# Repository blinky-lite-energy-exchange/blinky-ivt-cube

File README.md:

# Blinky IVT Cube
The Blinky-IVT cube controls an infrared diode to send pulses to an IVT heat pump. The pulse sequence is defined in the IVT.h file in the cubeCode folder. The pulse sequence was modified from [ToniA/arduino-heatpumpir](https://github.com/ToniA/arduino-heatpumpir). The [ToniA/arduino-heatpumpir](https://github.com/ToniA/arduino-heatpumpir) project contains pulse sequences for 29 different models of heat pumps so it possible to easily extend the Blinky IVT cube to many different models of heat pumps. The The microcontroller is a [Raspberry Pi Pico W](https://www.raspberrypi.com/products/raspberry-pi-pico/) that connects wirelessly to soft Blinky-Lite tray the resides on a Blinky-Lite box.

The Blinky IVT Cube sends and receives data from the [Blinky IVT tray](https://github.com/blinky-lite-energy-exchange/blinky-ivt-tray).

<br>

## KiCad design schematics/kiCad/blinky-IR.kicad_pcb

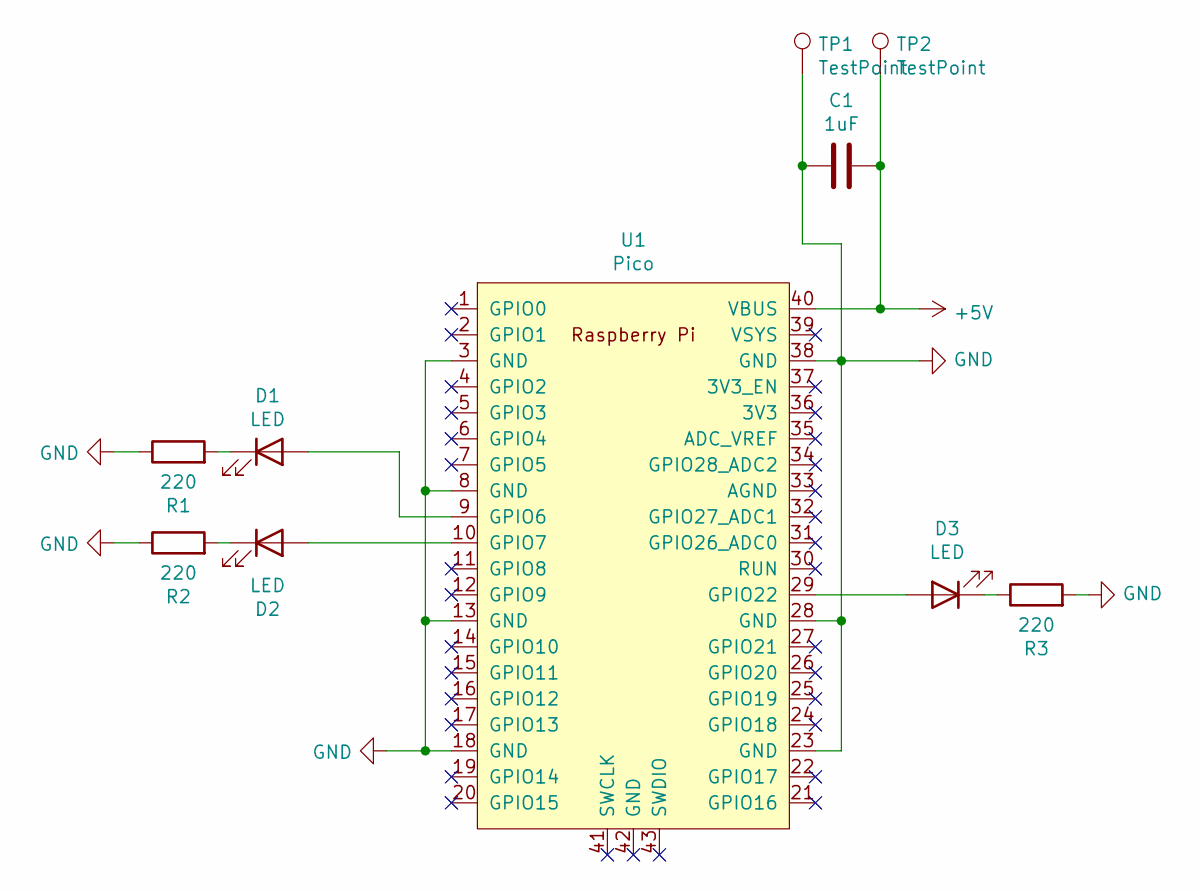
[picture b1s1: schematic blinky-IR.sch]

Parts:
C1: 1uF; C_1206_3216Metric_Pad1.42x1.75mm_HandSolder
D1, D2, D3: LED; LED_D5.0mm
R1, R2, R3: 220; R_1206_3216Metric_Pad1.42x1.75mm_HandSolder
TP1, TP2: TestPoint; TestPoint_THTPad_D2.0mm_Drill1.0mm
U1: Pico; RPi_Pico_SMD_TH

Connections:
+5V: C1.1, TP2.1, U1.40 (VBUS)
GND: C1.2, R1.1, R2.1, R3.2, TP1.1, U1.3 (GND), U1.8 (GND), U1.13 (GND), U1.18 (GND), U1.23 (GND), U1.28 (GND), U1.38 (GND)
unnamed: D1.1 (K), R1.2
unnamed: D1.2 (A), U1.9 (GPIO6)
unnamed: D2.1 (K), R2.2
unnamed: D2.2 (A), U1.10 (GPIO7)
unnamed: D3.1 (K), R3.1
unnamed: D3.2 (A), U1.29 (GPIO22)

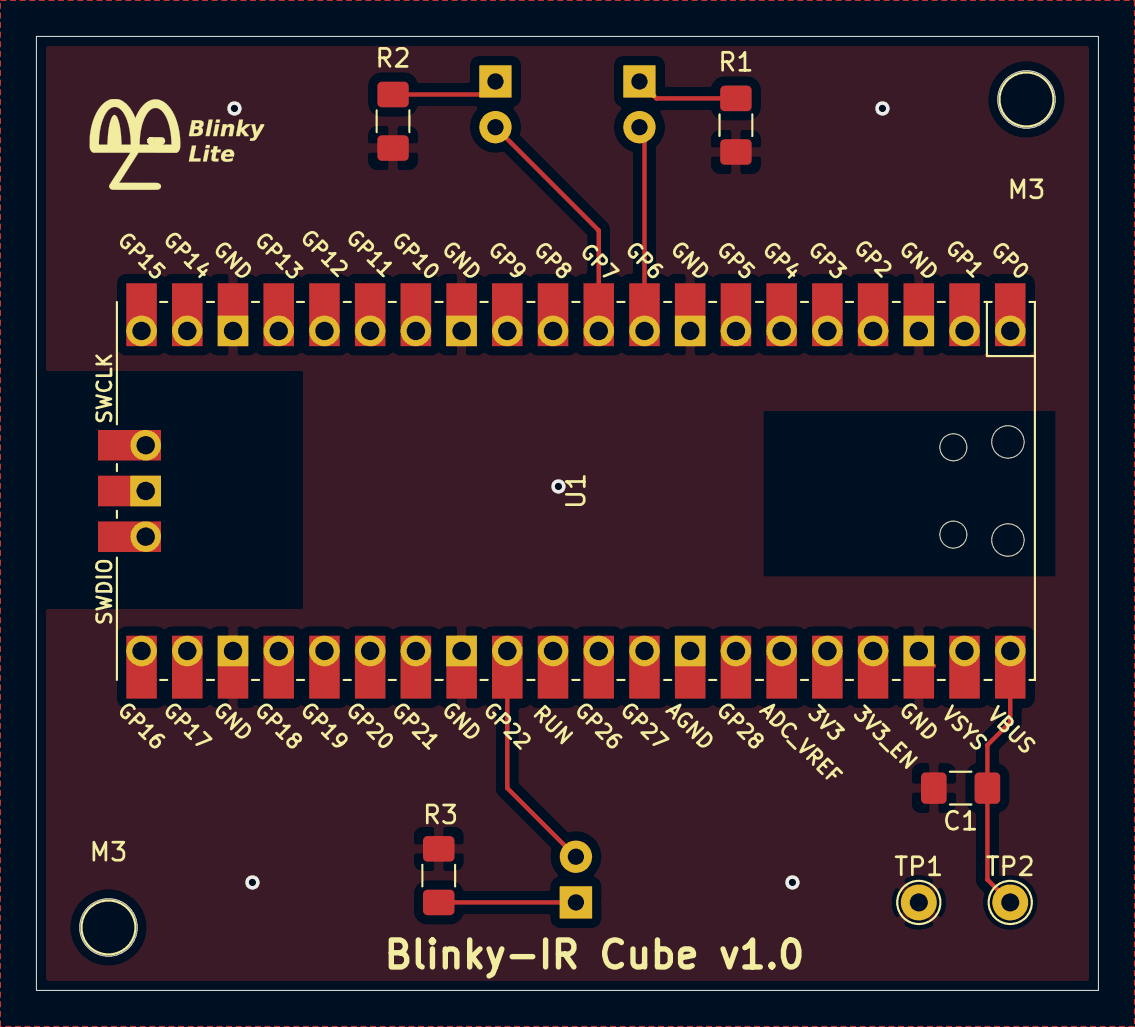
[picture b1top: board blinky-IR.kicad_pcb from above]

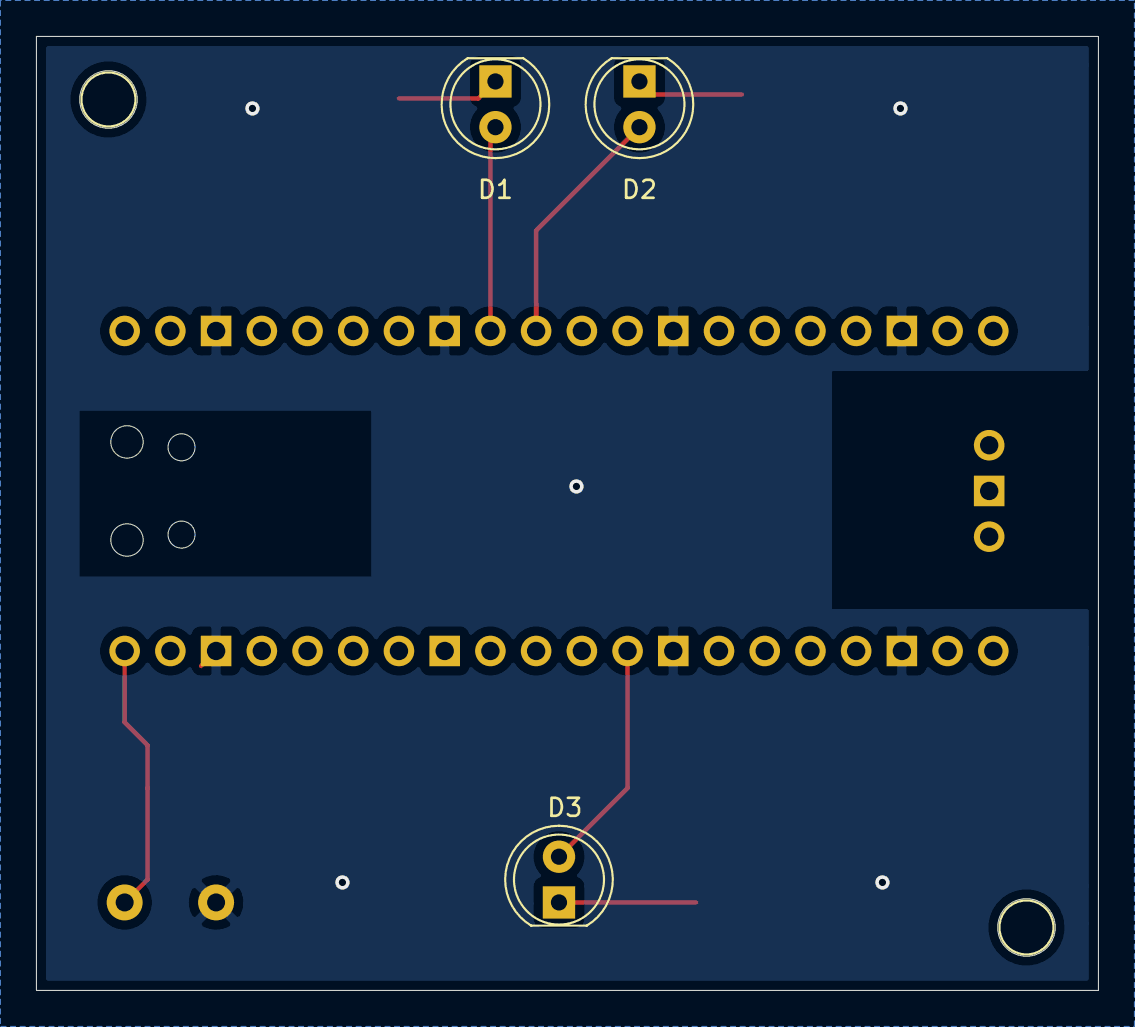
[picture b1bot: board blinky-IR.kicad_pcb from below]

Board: 2 copper layers, 59.0 x 53.0 mm, 12 parts (3 on the bottom side), 8 nets.

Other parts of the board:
M3, M3#2: MountingHole_3.2mm_M3

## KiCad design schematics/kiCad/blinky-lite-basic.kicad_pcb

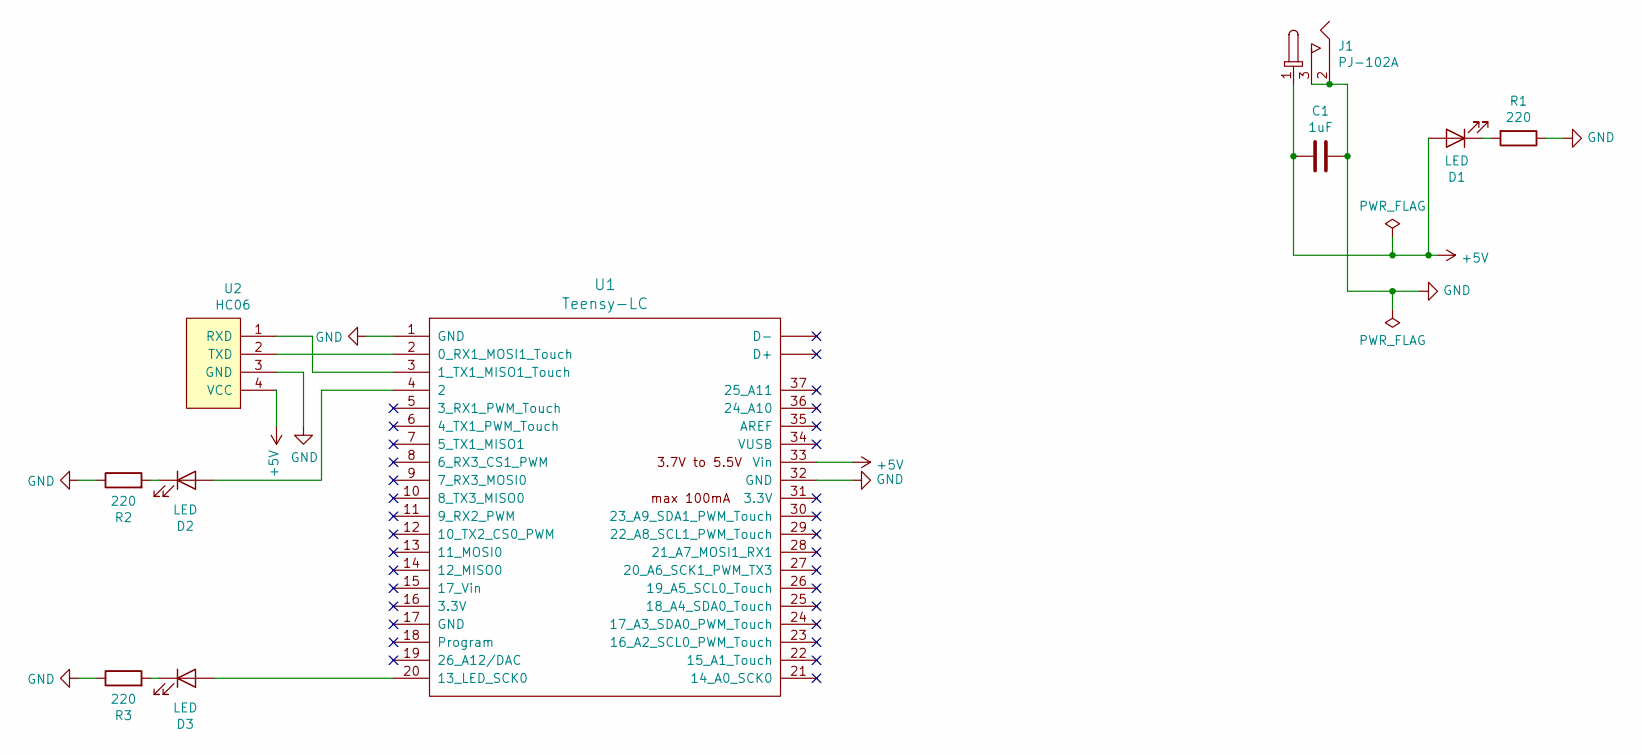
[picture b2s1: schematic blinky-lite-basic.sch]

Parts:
C1: 1uF; C_1206_3216Metric_Pad1.42x1.75mm_HandSolder
D1, D2, D3: LED; LED_D5.0mm
J1: PJ-102A; DC21Jack
R1, R2, R3: 220; R_1206_3216Metric_Pad1.42x1.75mm_HandSolder
U1: Teensy-LC; Teensy30_31_32_LC
U2: HC06

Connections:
+5V: C1.2, D1.2 (A), J1.1, U1.33 (Vin), U2.4 (VCC)
GND: C1.1, J1.2, J1.3, R1.1, R2.1, R3.1, U1.1 (GND), U1.32 (GND), U2.3 (GND)
unnamed: D1.1 (K), R1.2
unnamed: D2.1 (K), R2.2
unnamed: D2.2 (A), U1.4 (2)
unnamed: D3.1 (K), R3.2
unnamed: D3.2 (A), U1.20 (13_LED_SCK0)
unnamed: U1.2 (0_RX1_MOSI1_Touch), U2.2 (TXD)
unnamed: U1.3 (1_TX1_MISO1_Touch), U2.1 (RXD)

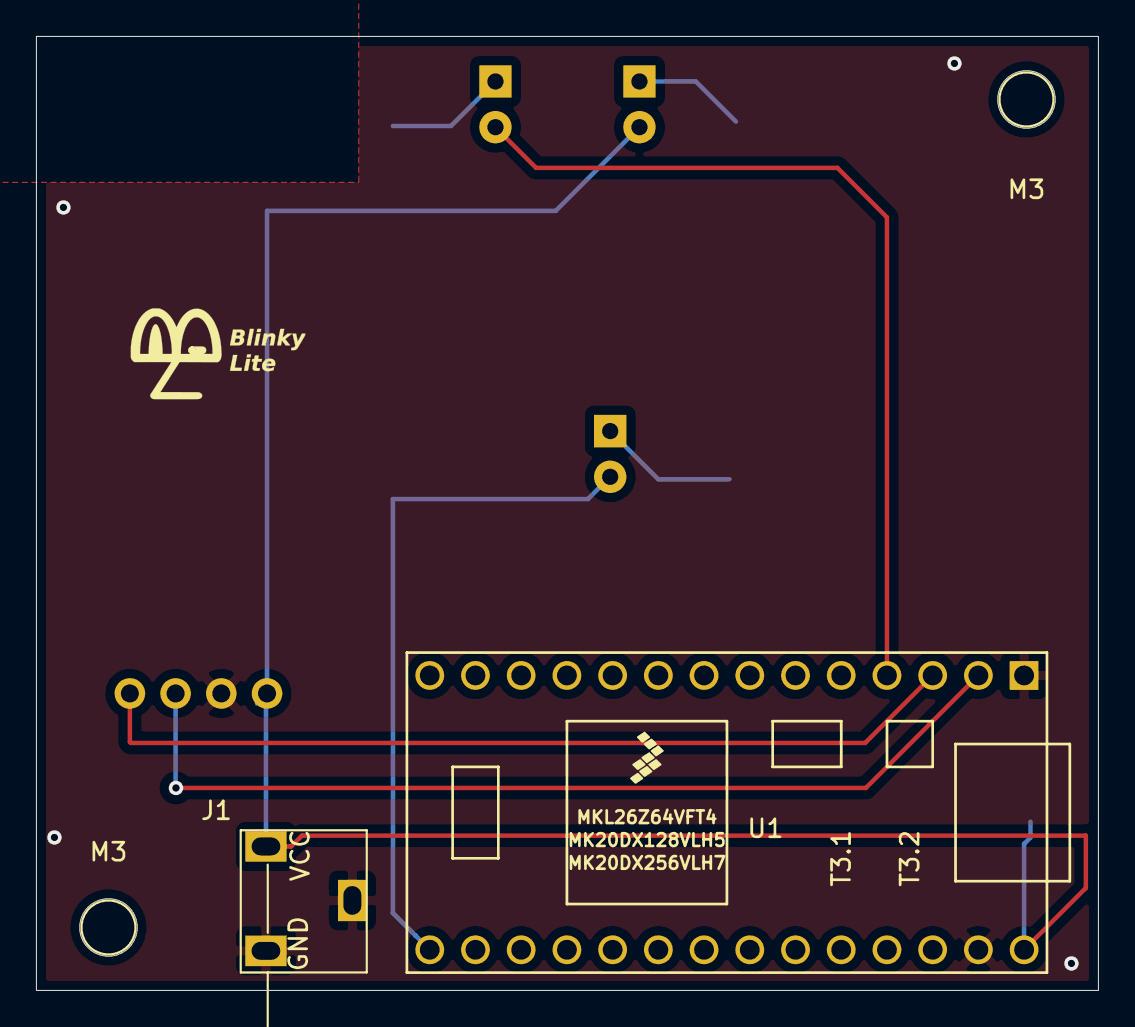
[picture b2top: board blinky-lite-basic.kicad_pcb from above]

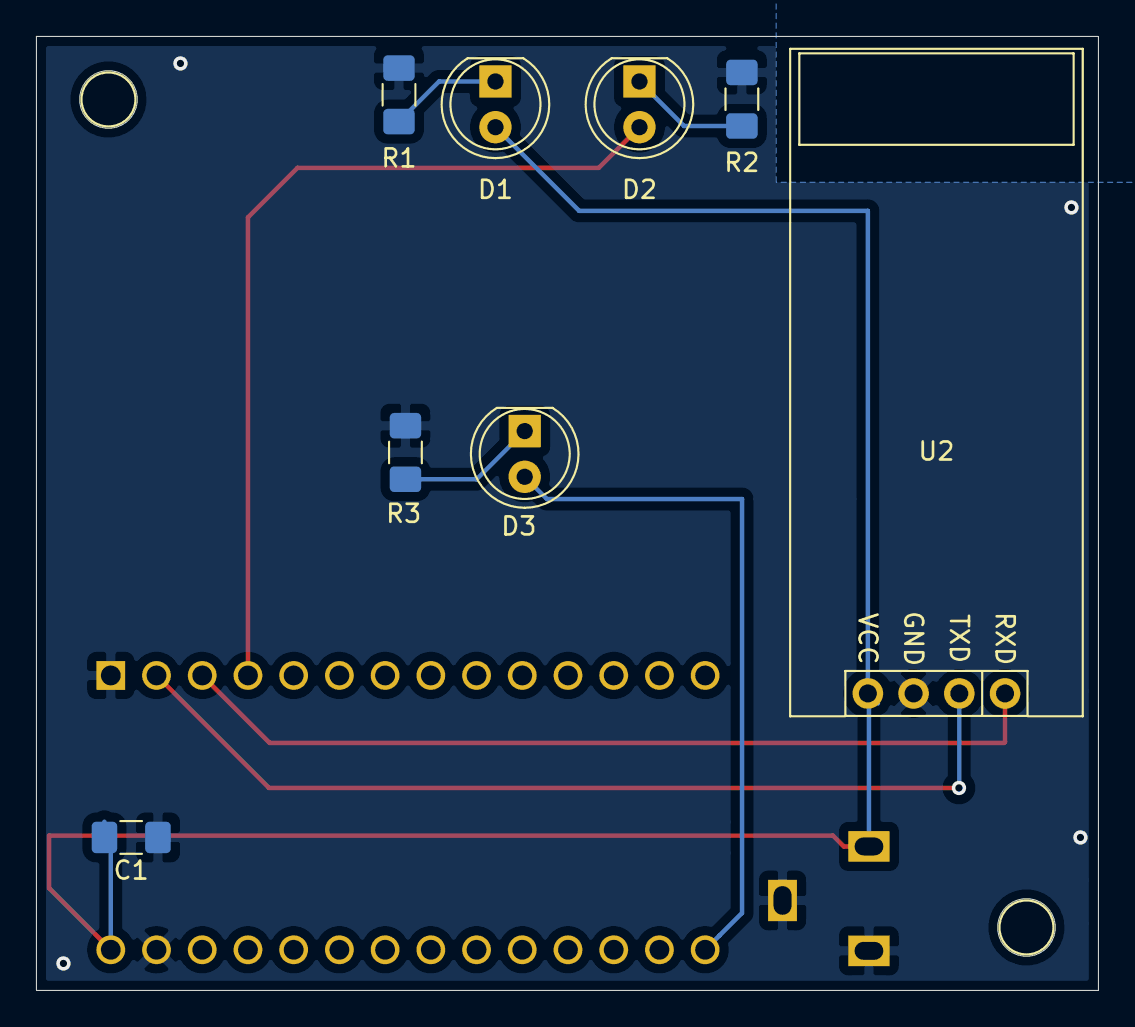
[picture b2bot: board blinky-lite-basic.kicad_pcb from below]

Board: 2 copper layers, 59.0 x 53.0 mm, 12 parts (8 on the bottom side), 9 nets.

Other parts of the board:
M3, M3#2: MountingHole_3.2mm_M3

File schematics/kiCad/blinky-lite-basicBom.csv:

Reference, Value, Footprint, Datasheet
"D1","LED","LED_THT:LED_D5.0mm","~"
"R1","220","Resistor_SMD:R_1206_3216Metric_Pad1.42x1.75mm_HandSolder","~"
"C1","1uF","Capacitor_SMD:C_1206_3216Metric_Pad1.42x1.75mm_HandSolder","~"
"U2","HC06","dmcginnis427:HC06",""
"J1","PJ-102A","dmcginnis427:DC21Jack",""
"U1","Teensy-LC","TeensyFootprints:Teensy30_31_32_LC",""
"D2","LED","LED_THT:LED_D5.0mm","~"
"R2","220","Resistor_SMD:R_1206_3216Metric_Pad1.42x1.75mm_HandSolder","~"
"D3","LED","LED_THT:LED_D5.0mm","~"
"R3","220","Resistor_SMD:R_1206_3216Metric_Pad1.42x1.75mm_HandSolder","~"

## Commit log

2022-10-02 bluetooth working
2022-10-03 added picoW to schematic
2022-10-23 working on picoW
2022-10-23 fixed watchodog rollover
2022-11-12 before upgrade
2022-11-12 new class structure for pico
2022-11-15 added rp watchdog
2022-11-17 fixed mqtt mem problem
